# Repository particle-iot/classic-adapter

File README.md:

# Particle Classic Adapter
*Design files for the classic adapter to allow mesh devices to plug into Photon or Electron circuits*

The Particle Classic Adapter lets you use your Asset Tracker, Relay Shield, or other third-party shields with our third generation developer kits. Plug your Argon, Boron, or Xenon into this adapter and continue development as usual!

The top of the adapter has female connectors for you to plug in the Particle Mesh device. The bottom has male header pins in the Particle legacy form-factor for devices such as the Electron, Photon, or the Core.

The legacy side (male pins on the bottom) are designed to fit an Electron. So when plugging into a Photon socket please make sure the B/C pins side are hanging off the end, not plugged into anything.

You cannot supply more than 3.3V to any pin on the Argon/Boron/Xenon (except VUSB and the USB connector).

**Note:** This product is a one-way adapter. That is, this product does not enable use of Adafruit FeatherWings with the Photon or Electron.

### Pin Map

|Legacy Device | Mesh Device|
|:-------------|:-----------|
|A0 |A0 |
|A1 |A1 |
|A2 |A2 |
|A3 |A3 |
|A4 |A4 |
|A5 |A5 |
|D0 |D0 (SDA) |
|D1 |D1 (SCL) |
|D2 |D2 |
|D3 |D3 |
|D4 |D4 |
|D5 |D5 |
|D6 |D6 |
|D7 |D7 |
|C5<sup>[1]</sup>  |D8 |
|TX |TX |
|RX |RX |
|B5<sup>[1]</sup>  |D11 (MISO) |
|WKP<sup>[1]</sup>  |D12 (MOSI)|
|DAC<sup>[1]</sup>  |D13 (SCK) |
|RST |RST |
|VIN |VUSB |
|3V3 |3V3 |

**Notes:**

<sup>[1]</sup> These pins are connected via jumper pads on the top. You can cut these jumper traces and rewire them to a different pin on the Mesh device if the need arises.

<sup>[2]</sup> Pins C0 to C4 and B0 to B4 on the Particle legacy device headers are not connected to anything.

<sup>[3]</sup> Pins MD, Li+, and EN on the Particle Mesh device are not connected to anything.

### I2C

I2C (Wire) can be used on D0 and D1. However, pins on the mesh devices are not 5V tolerant, so make sure you do not have pull-ups to 5V.

### SPI

It's not possible to use SPI with the classic adapter. The mesh SPI pins (MISO, MOSI, SCK) are not connected to pins that support SPI on the Electron or Photon (B5, WKP, DAC). The mesh SPI1 pins overlap the Electron/Photon SPI1 pins, however they're different!

| SPI1 | Classic | Mesh | 
| --- | --- | --- |
| SCK | D4 | D2 |
| MOSI | D2 | D3 |
| MISO | D3 | D4 |

### Other Features

The mesh devices do not support DAC or CAN, so those classic devices using those features won't work with the classic adapter.

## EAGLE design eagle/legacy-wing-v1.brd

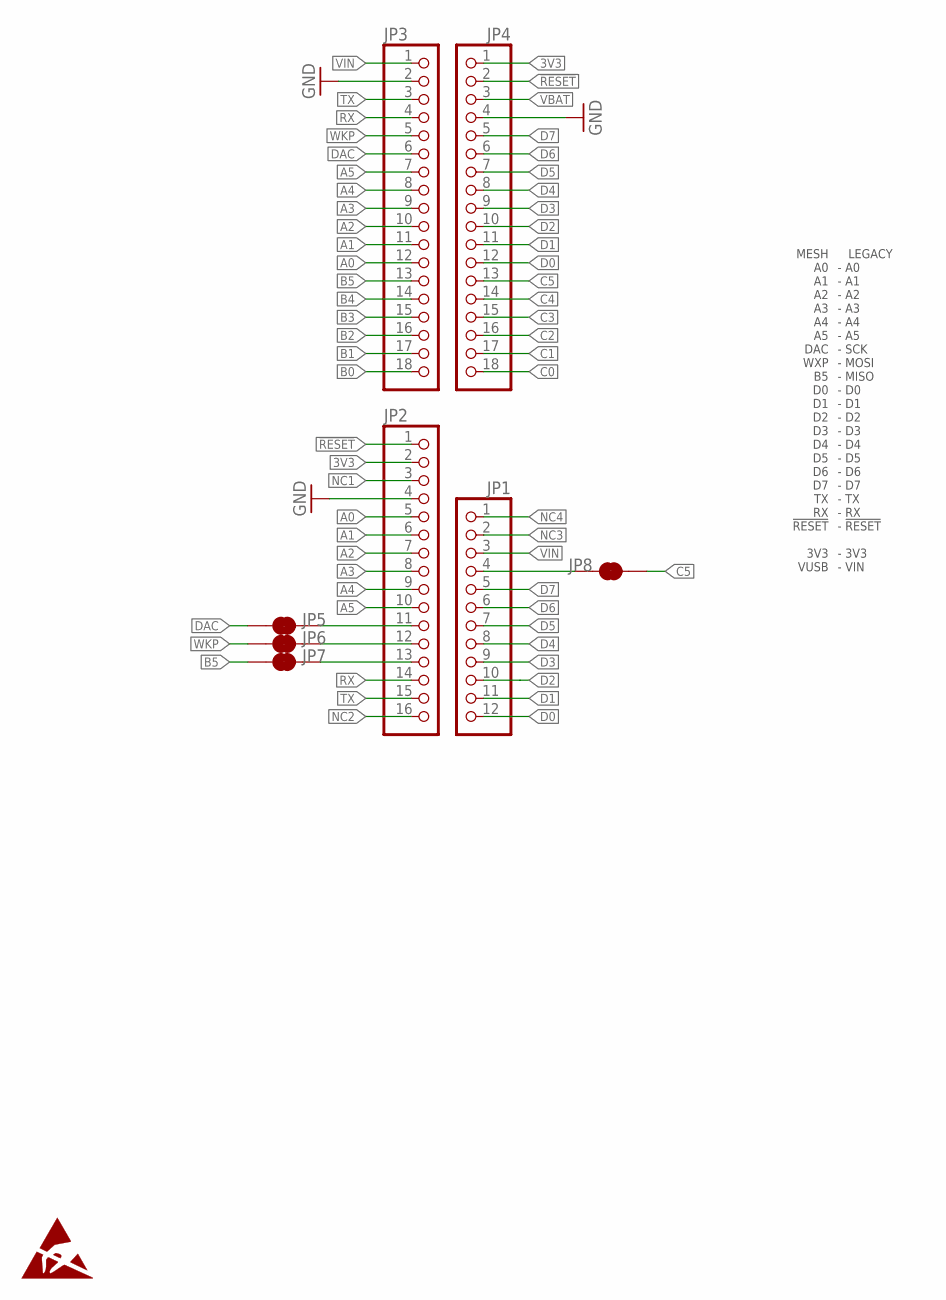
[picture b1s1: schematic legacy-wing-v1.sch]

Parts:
JP1: PINHD-1X121X12_SMT; 1X12_SMT
JP2: PINHD-1X161X16_SMT; 1X16_SMT
JP3, JP4: PINHD-1X181X18_SMT; 1X18_SMT
JP5, JP6, JP7, JP8: JUMPER-SMT_2_NC_TRACE_NO-SILK; SMT-JUMPER_2_NC_TRACE_NO-SILK

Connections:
3V3: JP2.2, JP4.1
!RESET: JP2.1, JP4.2
A0: JP2.5, JP3.12
A1: JP2.6, JP3.11
A2: JP2.7, JP3.10
A3: JP2.8, JP3.9
A4: JP2.9, JP3.8
A5: JP2.10, JP3.7
B0: JP3.18
B1: JP3.17
B2: JP3.16
B3: JP3.15
B4: JP3.14
B5: JP3.13, JP7.1
C0: JP4.18
C1: JP4.17
C2: JP4.16
C3: JP4.15
C4: JP4.14
C5: JP4.13, JP8.2
D0: JP1.12, JP4.12
D1: JP1.11, JP4.11
D2: JP1.10, JP4.10
D3: JP1.9, JP4.9
D4: JP1.8, JP4.8
D5: JP1.7, JP4.7
D6: JP1.6, JP4.6
D7: JP1.5, JP4.5
DAC: JP3.6, JP5.1
GND: JP2.4, JP3.2, JP4.4
unnamed: JP2.11, JP5.2
unnamed: JP2.12, JP6.2
unnamed: JP2.13, JP7.2
unnamed: JP1.4, JP8.1
NC1: JP2.3
NC2: JP2.16
NC3: JP1.2
NC4: JP1.1
RX: JP2.14, JP3.4
TX: JP2.15, JP3.3
VBAT: JP4.3
VIN: JP1.3, JP3.1
WKP: JP3.5, JP6.1

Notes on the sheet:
MESH A0 A1 A2 A3 A4 A5 DAC WXP B5 D0 D1 D2 D3 D4 D5 D6 D7 TX RX !RESET 3V3 VUSB
LEGACY - A0 - A1 - A2 - A3 - A4 - A5 - SCK - MOSI - MISO - D0 - D1 - D2 - D3 - D4 - D5 - D6 - D7 - TX - RX - !RESET - 3V3 - VIN

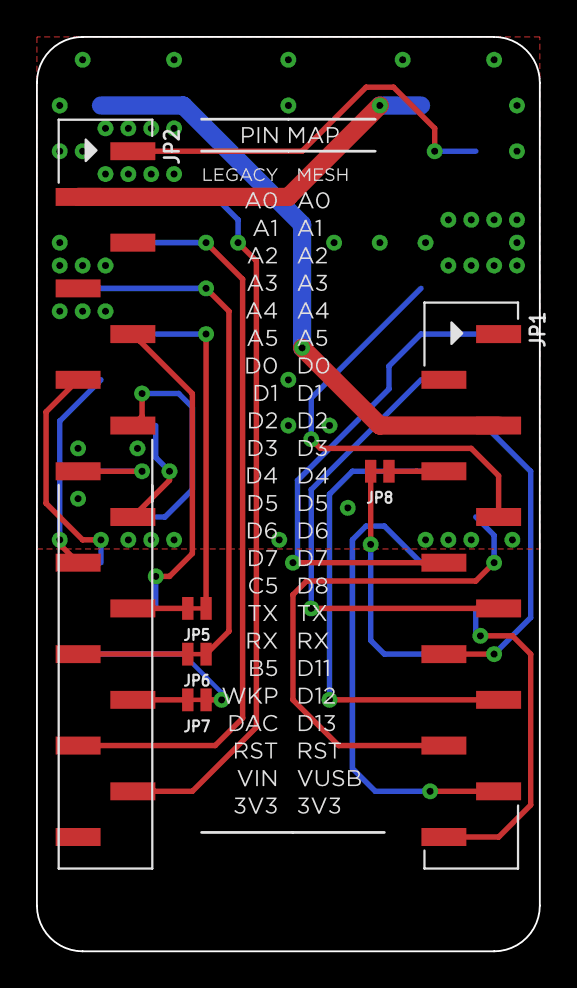
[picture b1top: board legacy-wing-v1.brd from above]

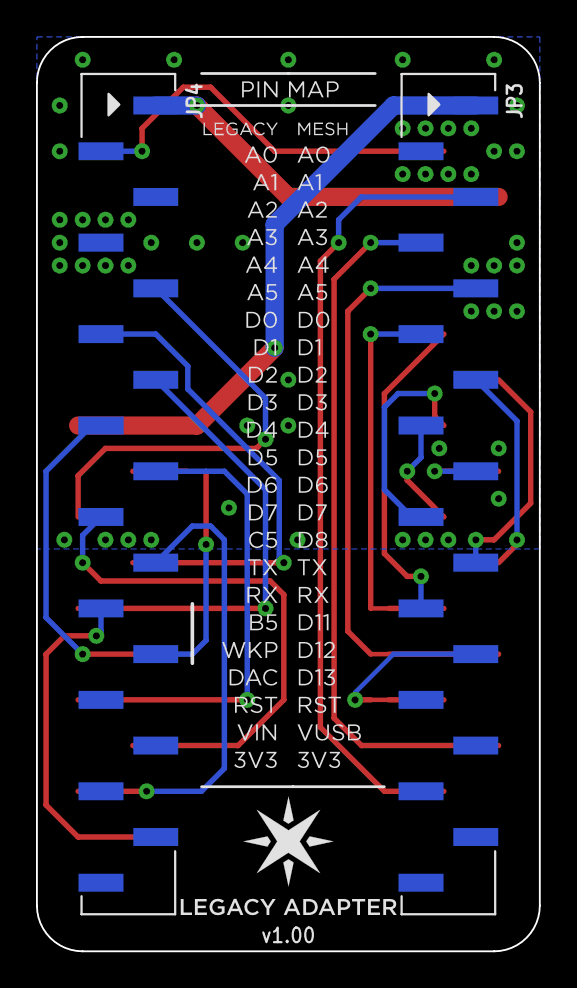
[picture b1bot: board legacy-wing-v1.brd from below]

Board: 2 copper layers, 27.9 x 50.8 mm, 9 parts (3 on the bottom side), 28 nets.

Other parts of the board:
U$1: PARTICLE_LOGO_5MM

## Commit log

2019-02-04 Public repo

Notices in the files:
parts and their libraries:
SparkFun-Jumpers: Licensing: Creative Commons ShareAlike 4.0 International - https://creativecommons.org/licenses/by-sa/4.0
